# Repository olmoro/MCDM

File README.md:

### <p align="center">MCDM - Moro Charge and Discharge Module
***
#### <p align="center"> Как это работает.
Зарядное устройство состоит из трех блоков.
Первый из них блок питания на 18 вольт соответствующей мощности, например [WX-DC2406](https://aliexpress.ru/item/1005001714079538.html?_ga=2.268223694.1168692661.1643047564-769654542.1642920280&sku_id=12000018559376968&spm=a2g39.orderlist.0.0.60754aa6RxSv8u) настроенный на выходное напряжение 18 вольт.

Второй блок - плата управления на микроконтроллере ESP-WROOM-32D - дисплей, кнопки, светодиодная индикация, USB интерфейс. Назначение - ввод-вывод пользовательских настроек, исполнение выбранного алгоритма работы, логирование и управление по каналу WiFi. Данные об этом блоке в своем депозитории.

Третий блок - зарядно-разрядный модуль. Силовая часть заимствована от [XL4016 DC-DC Max 9A 300W](https://aliexpress.ru/item/32661166685.html?_ga=2.264151500.1168692661.1643047564-769654542.1642920280&sku_id=12000020944321893&spm=a2g39.orderlist.0.0.60754aa6RxSv8u). Что от него осталось в итоге.

 Управляется субмодулем [WeMos D1 SAMD21 M0 Mini](https://aliexpress.ru/item/4001074203011.html?_ga=2.268755377.1168692661.1643047564-769654542.1642920280&sku_id=10000014182967685&spm=a2g39.orderlist.0.0.60754aa6RxSv8u).
Субмодуль микроконтроллера съемный, устанавливается на гиперболические [разъемы](https://aliexpress.ru/item/32358969925.html?_ga=2.23972602.1168692661.1643047564-769654542.1642920280&sku_id=58391393685&spm=a2g39.orderlist.0.0.41c74aa6suqlA3). Для работы с выходными ключами и питания субмодуля используются гальванически развязанные [источники](https://aliexpress.ru/item/1005003568781579.html?_ga=2.165478714.428003227.1651560775-769654542.1642920280&sku_id=12000026320337806&spm=a2g39.orderlist.0.0.50684aa6oqK3eu) мощностью 1 ватт. В свою очередь управляющие команды субмодуль получает по асинхронному интерфейсу от платы управления.
 Не отмыта пока.

На блоке есть разъем для подключения 8-канального [логического анализатора](https://aliexpress.ru/item/4000183609972.html?spm=a2g2w.productlist.0.0.33ca2d9fLvrncQ&sku_id=10000000674073904).

#### <p align="center">Измерение напряжения
Измерение напряжения на подключенной батарее производятся по 4-х контактной схеме, используя дифференциальное измерение в диапазоне от -1.5 до 20 вольт. Погрешность измерения __% ± __ед.мзр.

#### <p align="center">Измерение токов заряда и разряда
Измерение токов заряда и разряда производится одним шунтом, используется сдвиг по напряжению для возможности измерения токов разной полярности в диапазоне от -5 до +10 ампер (ограничивается мощностью блока питания).  Погрешность измерения __% ± __ед.мзр.

#### <p align="center">Управление разрядной схемой
Ток разряда задается 10-разрядным встроенным ЦАП с поддержанием тока ПИД-регулятором. Схема разряда заимствована от Кулона 912, ток задается выходом DAC микроконтроллера. Внешним ОУ диапазон выходного сигнала расширен до 5 вольт. Для облегчения теплового режима регулирующего MOSFET предусмотрен разъем подключения внешней нагрузки.

#### <p align="center">Управление выходными ключами
Для реализации безискрового подключения заряжаемой батареи ключевой каскад управляется синхронно с силовым преобразователем, а именно: при отключении, например при перегрузке, одновременно отключается и силовой преобразователь. Остаточный заряд снимается подключением разрядной цепи (этот ток не проходит через токоизмерительный шунт). То есть включение преобразователя без подключения измерителя и на ХХ невозможно. Имеется возможность нагружать преобразователь при работе на холостом ходу или незначительной нагрузке.

#### <p align="center">Регулирование мощности DC преобразователя.
Управление понижающим преобразователем производится ШИМ-сигналом частотой 190кГц посредством MIC4420. Для регулирования напряжения и токов используются ПИД-регуляторы. В режиме заряда или источника питания регуляторы напряжения и тока используют собственные настройки. Для монотонности и непрерывности выходной характеристики используется один и тот же экземпляр регулятора. Принцип переключения от поддержания тока к поддержанию напряжения и обратно соответствует аналоговому регулятору 912-го кулона. Коэффициенты допускается регулировать "на лету". Для реализации импульсных режимов предусмотрены сохранение и восстановление параметров регулирования, но задание временнЫх параметров (длительность импульсов, например) возлагается на главный контроллер. Регулирование ведется с фиксированной частотой 10 Гц. Все вычисления целочисленные, так что вычисление шага занимает лишь несколько микросекунд. С этой целью параметры управления драйверу передаются предвычисленными и целочисленными.

#### <p align="center">Интерфейс
Обмен с главным контроллером производится по асинхронному каналу на частоте 115200 бод. Протокол обмена [WAKE](https://eewiki.ru/wiki/%D0%A1%D0%BF%D0%B5%D1%86%D0%B8%D1%84%D0%B8%D0%BA%D0%B0%D1%86%D0%B8%D1%8F_%D0%BF%D1%80%D0%BE%D1%82%D0%BE%D0%BA%D0%BE%D0%BB%D0%B0_WAKE) предусматривает проверку целостности пакета и подтверждение приема. Ведущим контроллером является главный контроллер, в фоновом режиме опрашивающий драйвер и получающий пакет, содержащий измерения напряжения в милливольтах и ток в миллиамперах, а также информацию о состоянии. Управляющими командами производится включение-отключение DC источника и задание напряжения и тока для ПИД-регулятора. Предусматривается достаточное количество команд настройки АЦП, приборного смещения, калибровочных коэффициентов для  преобразования в физические величины, порогов срабатывания защиты и т.д. Для управления и настройки ПИД-регулятора, и ещё масса тестовых команд, надобность в которых практически отпала по ходу дела. Заводские и пользовательские установки хранятся в памяти управляющего контроллера и загружаться на этапе инициализации, заменяя параметры разработчика (defaults).

В директории Frames представлены данные для тестирования с помощью приложения WakeUsb.

#### <p align="center">Система охлаждения
Силовые элементы, [датчик температуры](https://aliexpress.ru/item/33014111002.html?spm=a2g2w.productlist.0.0.108e2a96XiZTKA&sku_id=67175460751) и [вентилятор](https://aliexpress.ru/item/4001029238958.html?spm=a2g2w.productlist.0.0.49696217XrQaE6&sku_id=10000013596178639) размещены на [радиаторе](https://aliexpress.ru/item/1005003036398261.html?_ga=2.156583358.428003227.1651560775-769654542.1642920280&sku_id=12000023368395685&spm=a2g39.orderlist.0.0.50684aa6xwye5Y) размером 100x60x10 мм. Регулирование производится ПИД-регулятором.

#### <p align="center">Печатная плата
115*65 мм двусторонняя 1oz. Схема, сборки, перечень элементов и гербер-файлы в директории Docements.

#### <p align="center">Формат реализованных команд управления.
##### <p align="center">(Не отредактировано)
Имя | Код | Параметр | Ответ | Примечание
--------------------------:|------:|-------:|-------------:|----------------------------------:
cmd_read_u_i|0x10|-|int int uint|Чтение напряжения,тока (мВ и мА) и состояния
cmd_get_u|0x11|-|int|Чтение напряжения (мВ)
cmd_get_i|0x12|-|int|Чтение тока (мА)
cmd_get_ui|0x13|-|int int|Чтение напряжения и тока (мВ и мА)
cmd_get_state|0x14|-|uint|Чтение состояния
cmd_get_state|0x15|-|uint|Чтение температуры радиатора
cmd_power_go|0x20|-|-|Старт преобразователя с заданными максимальными U и I
cmd_power_stop|0x21|-|-|Отключение ( и разряда в том числе)
cmd_set_pid|0x22|-|-|set all parameters (в разработке)
cmd_get_factor_u|0x30|-|uint|Чтение множителя преобразования в милливольты
cmd_set_factor_u|0x31|uint|-|Запись множителя преобразования в милливольты
cmd_set_factor_default_u|0x32|-|-|Возврат к заводскому множителю преобразования в милливольты
cmd_get_smooth_u|0x33|-|uint|Чтение параметра сглаживания по напряжению
cmd_set_smooth_u|0x34|uint|-|Запись параметра сглаживания по напряжению (1...3)
cmd_get_offset_u|0x35|-|uint|Чтение приборного смещения по напряжению
cmd_set_offset_u|0x36|int|-|Запись приборного смещения по напряжению
cmd_get_factor_i|0x38|-|uint|Чтение множителя преобразования в миллиамперы
cmd_set_factor_i|0x39|uint|-|Запись множителя преобразования в миллиамперы
cmd_set_factor_default_i|0x3A|-|-|Возврат к заводскому множителю преобразования в миллиамперы
cmd_get_smooth_i|0x3B|-|uint|Чтение параметра сглаживания по току
cmd_set_smooth_i|0x3C|uint|-|Запись параметра сглаживания по току (1...3)
cmd_get_offset_i|0x3D|-|uint|Чтение приборного смещения по току
cmd_set_offset_i|0x3E|int|-|Запись приборного смещения по току
cmd_pid_configure|0x40|uint uint uint uint uint uint|-|set mode,kp,ki,kd,min,max
cmd_pid_set_coefficients|0x41|uint uint uint|-|set kp, ki, kd
cmd_pid_output_range|0x42|uint uint|-|set min, max
cmd_pid_reconfigure|0x43|uint uint uint uint uint|-|set kp,ki,kd,min,max w/o clear
cmd_pid_clear|0x44|-|-|clear
cmd_pid_test|0x46|uint uint uint|-|mode, setpoint, sw
cmd_pid_get_configure|0x48|-|uint uint uint uint uint uint|mode,kP,kI,kD,min,max - возвращает параметры текущего режима регулирования
cmd_pid_set_max_sum|0x49|uint|-|Задает максимальный интеграл при вычислении шага рег.
cmd_set_cooler|0x4F|uint|-|Задать скорость вентилятора
cmd_adc_read_probes|0x50|-|int,int|Read all probes
cmd_adc_get_offset|0x51|-|int|Читать смещение АЦП
cmd_adc_set_offset|0x52|int|-|Запись смещения АЦП
cmd_set_switch_pin|0x54|?|-|sw_pin D4 PA14 ?
cmd_set_power|0x56|int|-|пользоваться с осторожностью - выяснение пределов регулирования
cmd_set_discharge|0x57|uint|-|не проверена
cmd_set_voltage|0x58|uint|-|старая, не проверена
cmd_set_current|0x59|uint|-|старая, не проверена
cmd_set_discurrent|0x5A|uint|-|старая, не проверена
cmd_set_surge_compensation|0x5B|?|-|параметры подавления всплеска напряжения na
cmd_set_idle_load|0x5C|uint|-|параметры доп.нагрузки ХХ
cmd_get_win_less_u|0x60|-|int|Порог отключения по Umin
cmd_set_win_less_u|0x61|int|-|Порог отключения по Umin
cmd_set_win_less_default_u|0x62|int|-|Порог отключения по Umin
cmd_get_win_up_u|0x63|-|int|Порог отключения по Umax
cmd_set_win_up_u|0x64|int|-|Порог отключения по Umax
cmd_set_win_up_default_u|0x65|int|-|Порог отключения по Umax
cmd_get_win_less_i|0x68|-|int|Порог отключения по Imin
cmd_set_win_less_i|0x69|int|-|Порог отключения по Imin
cmd_set_win_less_default_i|0x6A|int|-|Порог отключения по Imin
cmd_get_win_up_i|0x6B|-|int|Порог отключения по Imax
cmd_set_win_up_i|0x6C|int|-|Порог отключения по Imax  
cmd_set_win_up_default_i|0x6D|int|-|Порог отключения по Imax

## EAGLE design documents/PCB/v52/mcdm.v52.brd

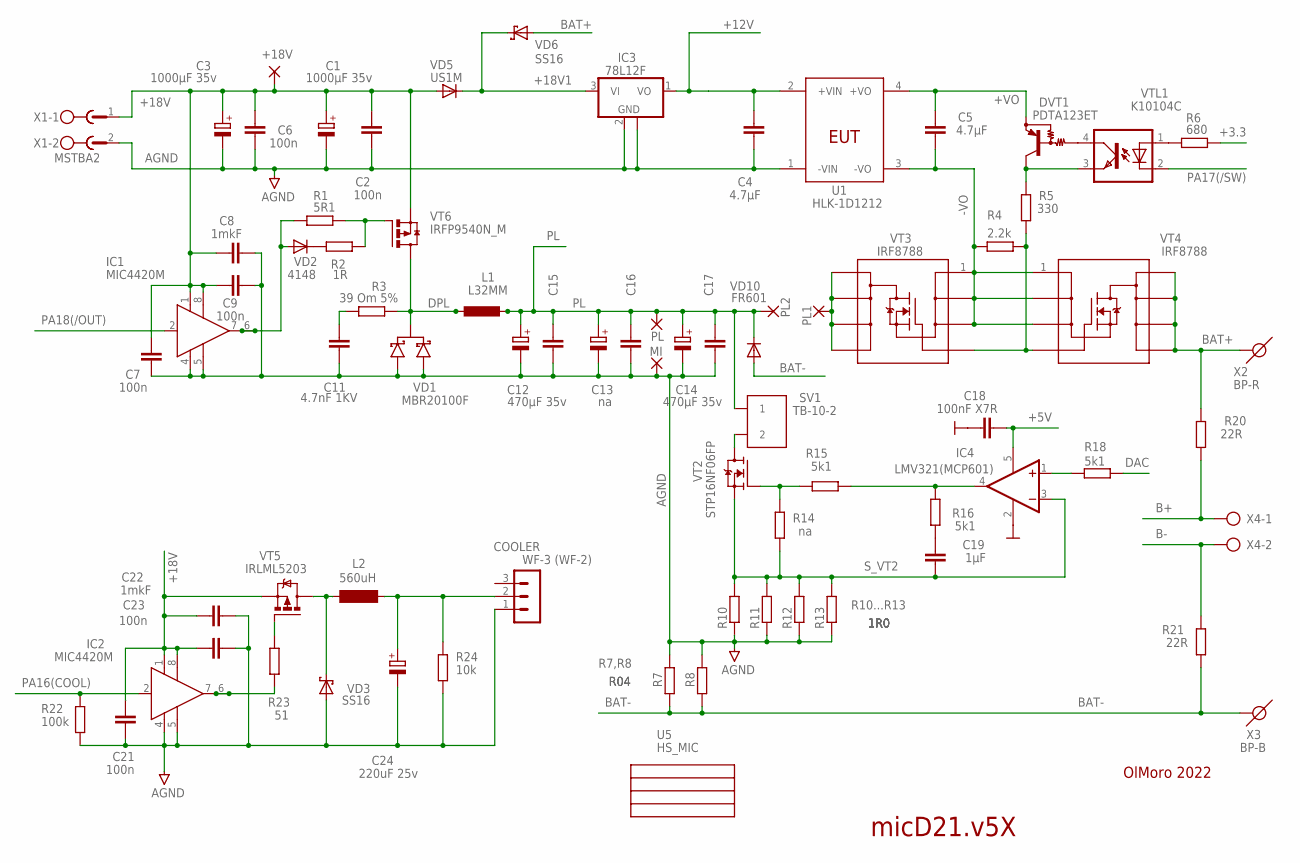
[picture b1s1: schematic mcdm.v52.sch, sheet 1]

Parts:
+18V: WIREPAD1,6/0,8; 1,6/0,8
C1, C3: 1000µF 35v; E5-10,5
C2, C6: 100n; C0805
C4, C5: 4.7µF; C0603
C7, C9, C21, C23: 100n; C0603
C8, C22: 1mkF; C0603
C11: 4.7nF 1KV; C102-064X133
C12, C14: 470µF 35v; E5-10,5
C13: na; E5-10,5
C15, C16, C17: 1mkF; C0805
C18: 100nF X7R; C0603
C19: 1µF; C0603
C24: 220uF 25v; E5-8,5
COOLER: WF-3 (WF-2); WF-3
DVT1: PDTA123ET; SC59-BEC
IC1, IC2: MIC4420M; SO-08
IC3: 78L12F; SOT89
IC4: LMV321(MCP601); SOT23-5
L1: L32MM; L22MM
L2: 560uH; BS11
MI: 4,16O1,6
PL: 4,16O1,6
PL1, PL2: 2,54/0,8
R1: 5R1; R0805
R2: 1R; R0805
R3: 39 Om 5%; 0515/20
R4: 2.2k; R0603
R5: 330; R0603
R6: 680; R0603
R7, R8: R04; R2512
R10, R11, R12, R13: 1R0; R2512
R14: na; R0603
R15, R16, R18: 5k1; R0603
R20, R21: 22R; R0603
R22: 100k; R0603
R23: 51; R0603
R24: 10k; R0603
SV1: TB-10-2
U1: HLK-1D1212
U5: HS_MIC; HS-MIC
VD1: MBR20100F; ITO220J
VD2: 4148; SMADIODE
VD3, VD6: SS16; DO214AC
VD5: US1M; DO214AC
VD10: FR601; DIODE-1_P6-15
VT2: STP16NF06FP; TO-220FP_M
VT3, VT4: IRF8788; SO-8
VT5: IRLML5203; MICRO3
VT6: IRFP9540N_M; TO-220FP_M
VTL1: K10104C; SMD4-7
X1: MSTBA2
X2: BP-R
X3: BP-B
X4: AK500/2-H

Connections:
+3.3: R6.1; also elsewhere on the board
+5V: C18.2, IC4.5 (V+); also elsewhere on the board
+12V: C4.2, IC3.1 (VO), U1.2 (+VIN); also elsewhere on the board
+18V: +18V.1, C1.+, C2.2, C3.+, C6.2, C7.2, C8.2, C9.2, C21.2, C22.2, C23.2, IC1.1 (VS), IC1.8 (VS1), IC2.1 (VS), IC2.8 (VS1), VD5.A, VT5.2 (S), VT6.3 (S), X1.1; also elsewhere on the board
+18V1: IC3.3 (VI), VD5.C, VD6.C; also elsewhere on the board
+VO: C5.2, DVT1.E, U1.4 (+VO)
-VO: C5.1, R4.2, U1.3 (-VO), VT3.1 (S), VT3.2 (S), VT3.3 (S), VT4.1 (S), VT4.2 (S), VT4.3 (S)
AGND: C1.-, C2.1, C3.-, C4.1, C6.1, C7.1, C8.1, C9.1, C11.2, C12.-, C13.-, C14.-, C15.2, C16.2, C17.2, C21.1, C22.1, C23.1, C24.-, COOLER.1, IC1.4 (GND), IC1.5 (GND1), IC2.4 (GND), IC2.5 (GND1), IC3.2 (GND), IC3.2@1 (GND), MI.1, R7.2, R8.2, R10.1, R11.1, R12.1, R13.1, R22.2, R24.2, U1.1 (-VIN), VD1.1 (A1), VD1.3 (A2), VD3.A, X1.2; also elsewhere on the board
B+: R20.1, X4.1; also elsewhere on the board
B-: R21.1, X4.2; also elsewhere on the board
BAT+: R20.2, VD6.A, VT4.5 (D), VT4.6 (D), VT4.7 (D), VT4.8 (D), X2.1
BAT-: R7.1, R8.1, R21.2, VD10.A, X3.1; also elsewhere on the board
DAC: R18.2; also elsewhere on the board
DPL: L1.2@7 (2), L1.2@8 (2), R3.1, VD1.2 (C), VT6.2 (D)
G: R4.1, R5.1, VT3.4 (G), VT4.4 (G)
GND: C18.1, IC4.2 (V-); also elsewhere on the board
unnamed: R6.2, VTL1.1 (A)
unnamed: R2.2, VD2.C
unnamed: IC1.6 (OUT), IC1.7 (OUT), R1.2, VD2.A
unnamed: R1.1, R2.1, VT6.1 (G)
unnamed: SV1.P$2 (2), VT2.2 (D)
unnamed: C11.1, R3.2
unnamed: IC2.6 (OUT), IC2.7 (OUT), R23.2
unnamed: R23.1, VT5.1 (G)
unnamed: L2.1, VD3.C, VT5.3 (D)
unnamed: C24.+, COOLER.2, L2.2, R24.1
unnamed: R14.2, R15.2, VT2.1 (G)
unnamed: IC4.1 (+IN), R18.1
unnamed: C19.1, R16.2
unnamed: DVT1.C, R5.2, VTL1.3 (EMIT)
unnamed: DVT1.B, VTL1.4 (COL)
PA16(COOL): IC2.2 (IN), R22.1; also elsewhere on the board
PA17(/SW): VTL1.2 (C); also elsewhere on the board
PA18(/OUT): IC1.2 (IN); also elsewhere on the board
PL: C12.+, C13.+, C14.+, C15.1, C16.1, C17.1, L1.1, L1.1@2 (1), PL.1, PL2.1, SV1.P$1 (1), VD10.C
PL1: PL1.1, VT3.5 (D), VT3.6 (D), VT3.7 (D), VT3.8 (D)
S_VT2: C19.2, IC4.3 (-IN), R10.2, R11.2, R12.2, R13.2, R14.1, VT2.3 (S)
UDAC: IC4.4 (OUT), R15.1, R16.1

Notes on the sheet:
micD21.v5X
R10...R13
R7,R8
OlMoro 2022

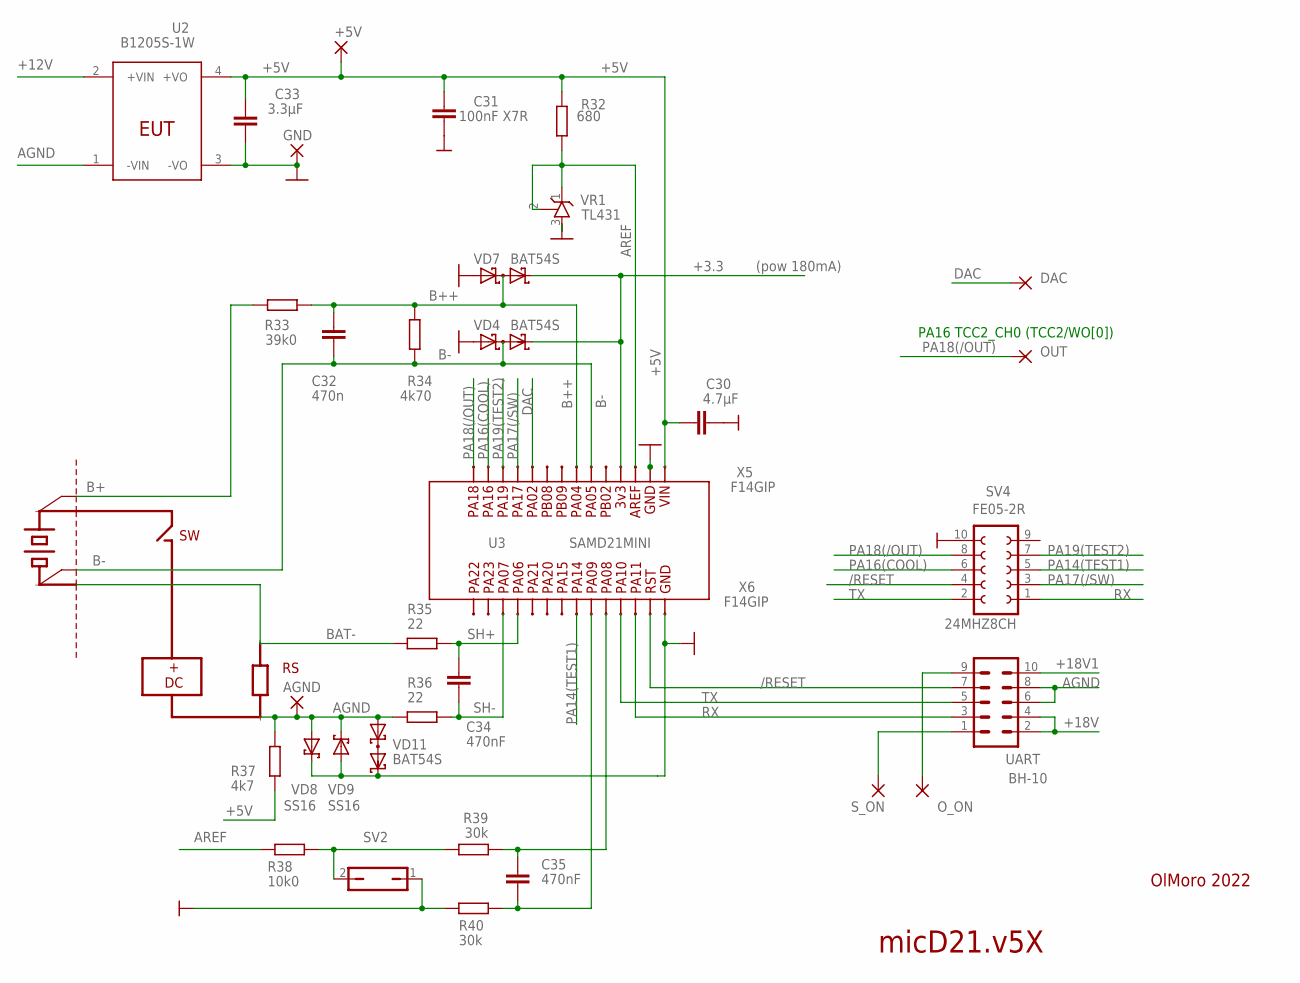
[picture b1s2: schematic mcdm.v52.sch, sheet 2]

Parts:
24MHZ8CH: DIAGNOSTICS
+5V: 1,6/0,8
AGND: AGND; 4,16O1,6
C30: 4.7µF; C0805
C31: 100nF X7R; C0603
C32: 470n; C0603
C33: 3.3µF; C0805
C34, C35: 470nF; C0603
DAC: 1,6/0,8
GND: GND; 4,16O1,6
OUT: 1,6/0,8
O_ON: 1,6/0,8
R32: 680; R0603
R33: 39k0; R0603
R34: 4k70; R0603
R35, R36: 22; R0603
R37: 4k7; R0603
R38: 10k0; R0603
R39, R40: 30k; R0603
SV2: JP1Q; JP1
SV4: FE05-2R
S_ON: 1,6/0,8
U2: B1205S-1W; HLK-1D1212
U3: SAMD21MINI
UART: BH-10; ML10
VD4, VD7, VD11: BAT54S; SOT23
VD8, VD9: SS16; DO214AC
VR1: TL431; SOT23
X5, X6: F14GIP

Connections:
+3.3: VD4.2 (C2), VD7.2 (C2), X5.4; also elsewhere on the board
+5V: +5V.1, C30.1, C31.1, C33.1, R32.1, R37.2, U2.4 (+VO), X5.1; also elsewhere on the board
+12V: U2.2 (+VIN); also elsewhere on the board
+18V: UART.2, UART.4; also elsewhere on the board
+18V1: UART.10; also elsewhere on the board
/OUT_ON: O_ON.1, UART.9
/RESET: SV4.4, UART.7, X6.13
/S_ON: S_ON.1, UART.1
AGND: AGND.1, R36.2, R37.1, U2.1 (-VIN), UART.6, UART.8, VD8.A, VD9.C, VD11.1 (A1); also elsewhere on the board
AREF: R32.2, R38.1, VR1.1 (C), VR1.2 (R), X5.3
B+: R33.2; also elsewhere on the board
B++: C32.1, R33.1, R34.1, VD7.3 (C1A2), X5.7
B-: C32.2, R34.2, VD4.3 (C1A2), X5.6; also elsewhere on the board
BAT-: R35.2; also elsewhere on the board
CELSIUS: C35.1, R39.2, X6.10
DAC: DAC.1, X5.10; also elsewhere on the board
GND: C30.2, C31.2, C33.2, GND.1, R40.1, SV2.1, SV4.10, U2.3 (-VO), VD4.1 (A1), VD7.1 (A1), VD8.C, VD9.A, VD11.2 (C2), VR1.3 (A), X5.2, X6.14; also elsewhere on the board
unnamed: C35.2, R40.2, X6.9
unnamed: R38.2, R39.1, SV2.2
PA14(TEST1): SV4.5, X6.8
PA16(COOL): SV4.6, X5.13; also elsewhere on the board
PA17(/SW): SV4.3, X5.11; also elsewhere on the board
PA18(/OUT): OUT.1, SV4.8, X5.14; also elsewhere on the board
PA19(TEST2): SV4.7, X5.12
RX: SV4.1, UART.3, X6.12
SH+: C34.1, R35.1, X6.4
SH-: C34.2, R36.1, X6.3
TX: SV4.2, UART.5, X6.11

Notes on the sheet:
micD21.v5X
+ DC
PA16 TCC2_CH0 (TCC2/WO[0])
(pow 180mA)
OlMoro 2022

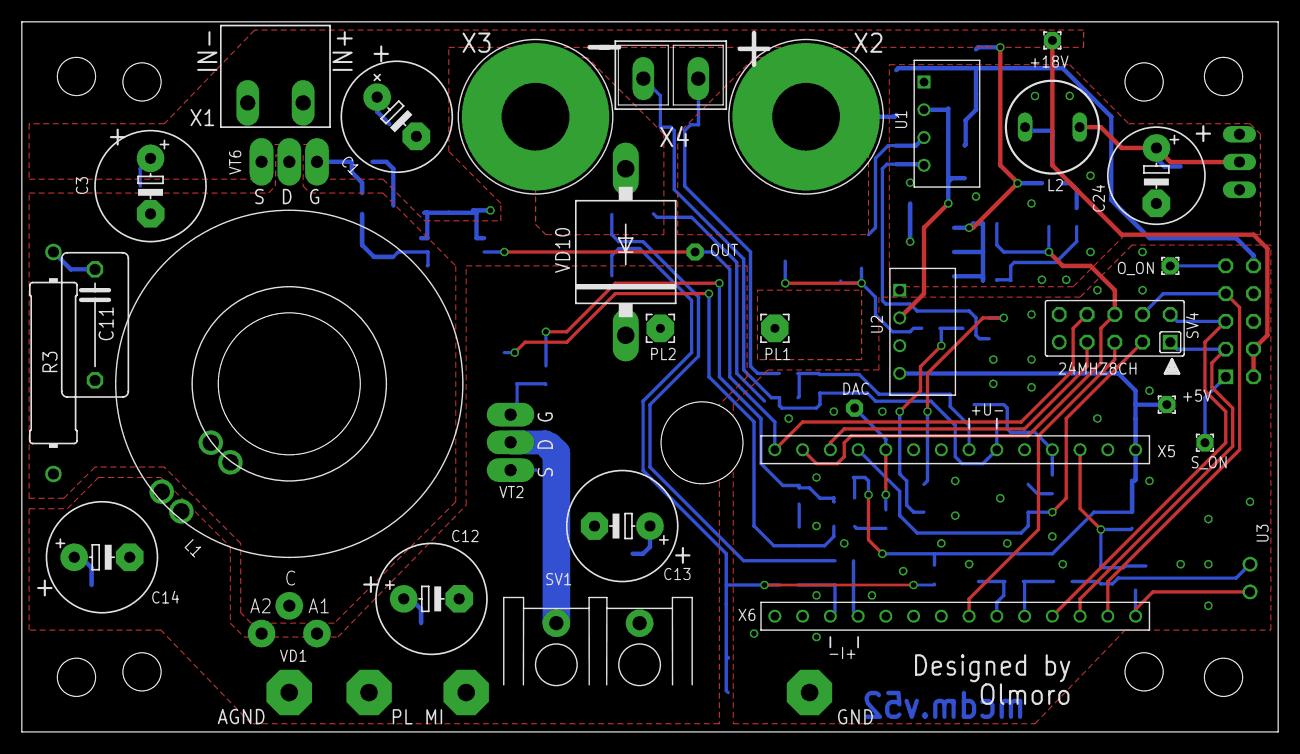
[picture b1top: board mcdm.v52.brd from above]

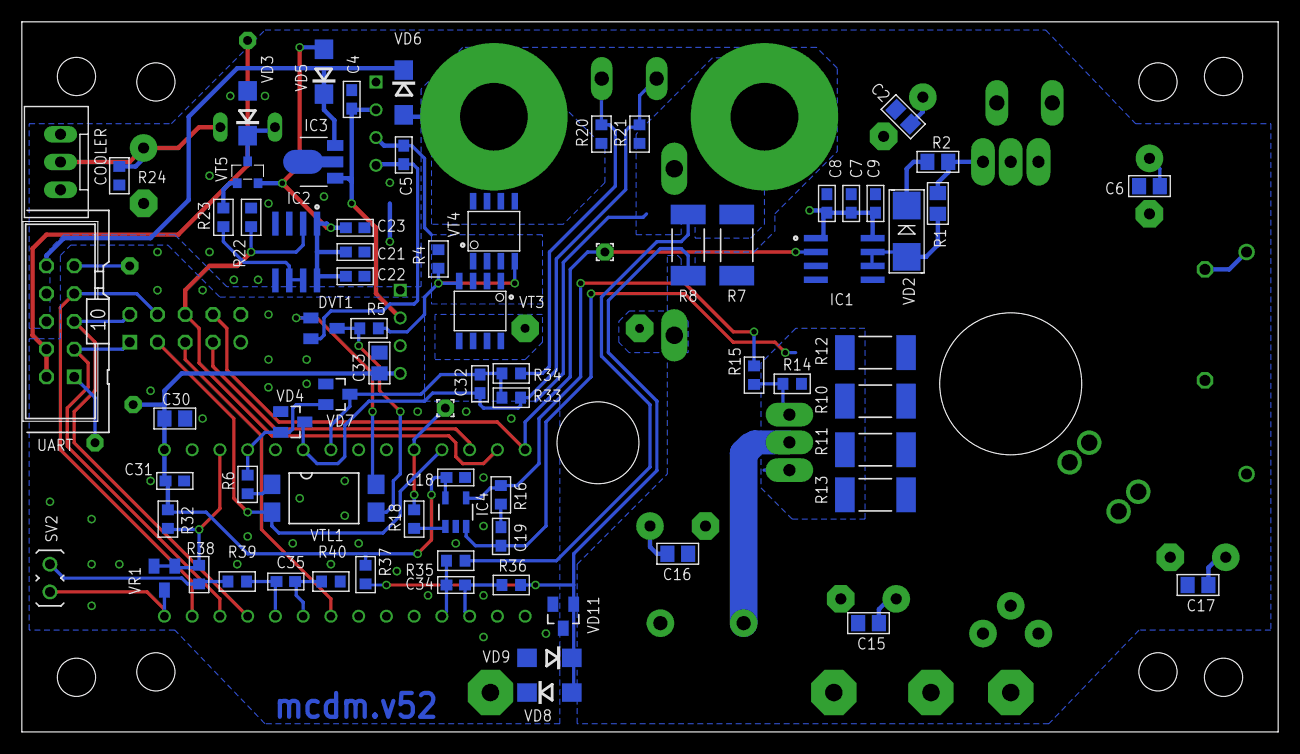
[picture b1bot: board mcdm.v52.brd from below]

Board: 2 copper layers, 115.0 x 65.0 mm, 111 parts (76 on the bottom side), 52 nets.

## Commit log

2022-01-27 Readme
2022-02-19 History PWM tab
2022-03-05 Test pins
2022-03-08 PWMs to PA16, PA18
    Для совместимости с выбранной библиотекой Turbo_PWM
2022-03-08 pwm optimization
2022-03-15 power test
2022-03-24 эксперименты с шим
2022-04-16 new variant.h
2022-04-21 test 9V 1A
2022-04-23 dac test
2022-04-23 v51a1 sch
2022-04-27 test
2022-04-28 pcb v52 added
2022-05-03 PCB_v53 added
2022-05-05 cooler
2022-05-05 pwm cool
2022-05-07 pwm optim
2022-05-08 sw off/on
2022-05-22 History
2022-05-24 test pwm
2022-05-26 test PID
2022-05-27 Калибровки
2022-06-06 230400
2022-06-07 New PowerStop (0x21)
2022-06-13 doPid()
2022-06-14 pid test
2022-06-15 Test U_MODE
2022-06-15 Test MODE_I
2022-06-17 Test pid U, I
2022-06-18 bits=9
2022-06-19 Kp Ki Kd
2022-06-21 Настройки ПИД
2022-06-22 ПИД тест
2022-07-01 пид множитель 12бит
2022-07-03 testModeD
2022-07-03 v0.1
2022-07-03 hist
2022-07-05 wo EEPROM
2022-07-09 Reply
2022-07-09 Replay
2022-07-13 New M0
2022-07-19 0x47
2022-07-20 garbage collection
2022-07-22 mestake

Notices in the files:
parts and their libraries:
microbuilder: This work is placed in the public domain, and may be freely used for commercial and non-commercial work with the following conditions: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
